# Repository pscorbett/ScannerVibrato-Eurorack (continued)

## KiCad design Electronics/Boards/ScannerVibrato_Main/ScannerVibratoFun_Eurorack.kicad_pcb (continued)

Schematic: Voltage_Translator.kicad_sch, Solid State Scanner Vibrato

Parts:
C45, C46: 100nF; C_0603_1608Metric
R3, R5, R6, R7, R8, R9: 100k; R_0603_1608Metric
U33: LM339; TSSOP-14_4.4x5mm_P0.65mm; Part Number LM339APWR

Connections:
+5V: R3.1; also elsewhere on the board
+9V: C45.1, R6.1, R7.1, R8.1, R9.1, U33.3 (V+); also elsewhere on the board
-9V: C46.2, U33.12 (V-); also elsewhere on the board
/Counters/TAP_MUXL_ODD_S0: U33.5 (+); also elsewhere on the board
/Counters/TAP_MUXL_ODD_S1: U33.7 (+); also elsewhere on the board
/Counters/TAP_MUXL_ODD_S2: U33.11 (+); also elsewhere on the board
/Counters/TAP_MUXL_ODD_S3: U33.9 (+); also elsewhere on the board
/Counters/X_TAP_MUXL_ODD_S0: R6.2, U33.2; also elsewhere on the board
/Counters/X_TAP_MUXL_ODD_S1: R7.2, U33.1; also elsewhere on the board
/Counters/X_TAP_MUXL_ODD_S2: R8.2, U33.13; also elsewhere on the board
/Counters/X_TAP_MUXL_ODD_S3: R9.2, U33.14; also elsewhere on the board
GND: C45.2, C46.1, R5.2; also elsewhere on the board
unnamed: R3.2, R5.1, U33.4 (-), U33.6 (-), U33.8 (-), U33.10 (-)

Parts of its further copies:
C49, C50, C53, C54, C57, C58: 100nF; C_0603_1608Metric
R10, R11, R12, R13, R14, R15, R16, R17, R18, R19, R20, R21, R22, R23, R24, R25, R26, R31: 100k; R_0603_1608Metric
U34, U35, U36: LM339; TSSOP-14_4.4x5mm_P0.65mm; Part Number LM339APWR

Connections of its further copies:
+5V: R10.1, R16.1, R22.1; also elsewhere on the board
+9V: C49.1, C53.1, C57.1, R12.1, R13.1, R14.1, R15.1, R18.1, R19.1, R20.1, R21.1, R24.1, R25.1, R26.1, R31.1, U34.3 (V+), U35.3 (V+), U36.3 (V+); also elsewhere on the board
-9V: C50.2, C54.2, C58.2, U34.12 (V-), U35.12 (V-), U36.12 (V-); also elsewhere on the board
/Counters/TAP_MUXL_EVEN_S0: U34.5 (+); also elsewhere on the board
/Counters/TAP_MUXL_EVEN_S1: U34.7 (+); also elsewhere on the board
/Counters/TAP_MUXL_EVEN_S2: U34.11 (+); also elsewhere on the board
/Counters/TAP_MUXL_EVEN_S3: U34.9 (+); also elsewhere on the board
/Counters/TAP_MUXR_EVEN_S0: U36.5 (+); also elsewhere on the board
/Counters/TAP_MUXR_EVEN_S1: U36.7 (+); also elsewhere on the board
/Counters/TAP_MUXR_EVEN_S2: U36.11 (+); also elsewhere on the board
/Counters/TAP_MUXR_EVEN_S3: U36.9 (+); also elsewhere on the board
/Counters/TAP_MUXR_ODD_S0: U35.5 (+); also elsewhere on the board
/Counters/TAP_MUXR_ODD_S1: U35.7 (+); also elsewhere on the board
/Counters/TAP_MUXR_ODD_S2: U35.11 (+); also elsewhere on the board
/Counters/TAP_MUXR_ODD_S3: U35.9 (+); also elsewhere on the board
/Counters/X_TAP_MUXL_EVEN_S0: R12.2, U34.2; also elsewhere on the board
/Counters/X_TAP_MUXL_EVEN_S1: R13.2, U34.1; also elsewhere on the board
/Counters/X_TAP_MUXL_EVEN_S2: R14.2, U34.13; also elsewhere on the board
/Counters/X_TAP_MUXL_EVEN_S3: R15.2, U34.14; also elsewhere on the board
/Counters/X_TAP_MUXR_EVEN_S0: R24.2, U36.2; also elsewhere on the board
/Counters/X_TAP_MUXR_EVEN_S1: R25.2, U36.1; also elsewhere on the board
/Counters/X_TAP_MUXR_EVEN_S2: R26.2, U36.13; also elsewhere on the board
/Counters/X_TAP_MUXR_EVEN_S3: R31.2, U36.14; also elsewhere on the board
/Counters/X_TAP_MUXR_ODD_S0: R18.2, U35.2; also elsewhere on the board
/Counters/X_TAP_MUXR_ODD_S1: R19.2, U35.1; also elsewhere on the board
/Counters/X_TAP_MUXR_ODD_S2: R20.2, U35.13; also elsewhere on the board
/Counters/X_TAP_MUXR_ODD_S3: R21.2, U35.14; also elsewhere on the board
GND: C49.2, C50.1, C53.2, C54.1, C57.2, C58.1, R11.2, R17.2, R23.2; also elsewhere on the board
unnamed: R10.2, R11.1, U34.4 (-), U34.6 (-), U34.8 (-), U34.10 (-)
unnamed: R16.2, R17.1, U35.4 (-), U35.6 (-), U35.8 (-), U35.10 (-)
unnamed: R22.2, R23.1, U36.4 (-), U36.6 (-), U36.8 (-), U36.10 (-)

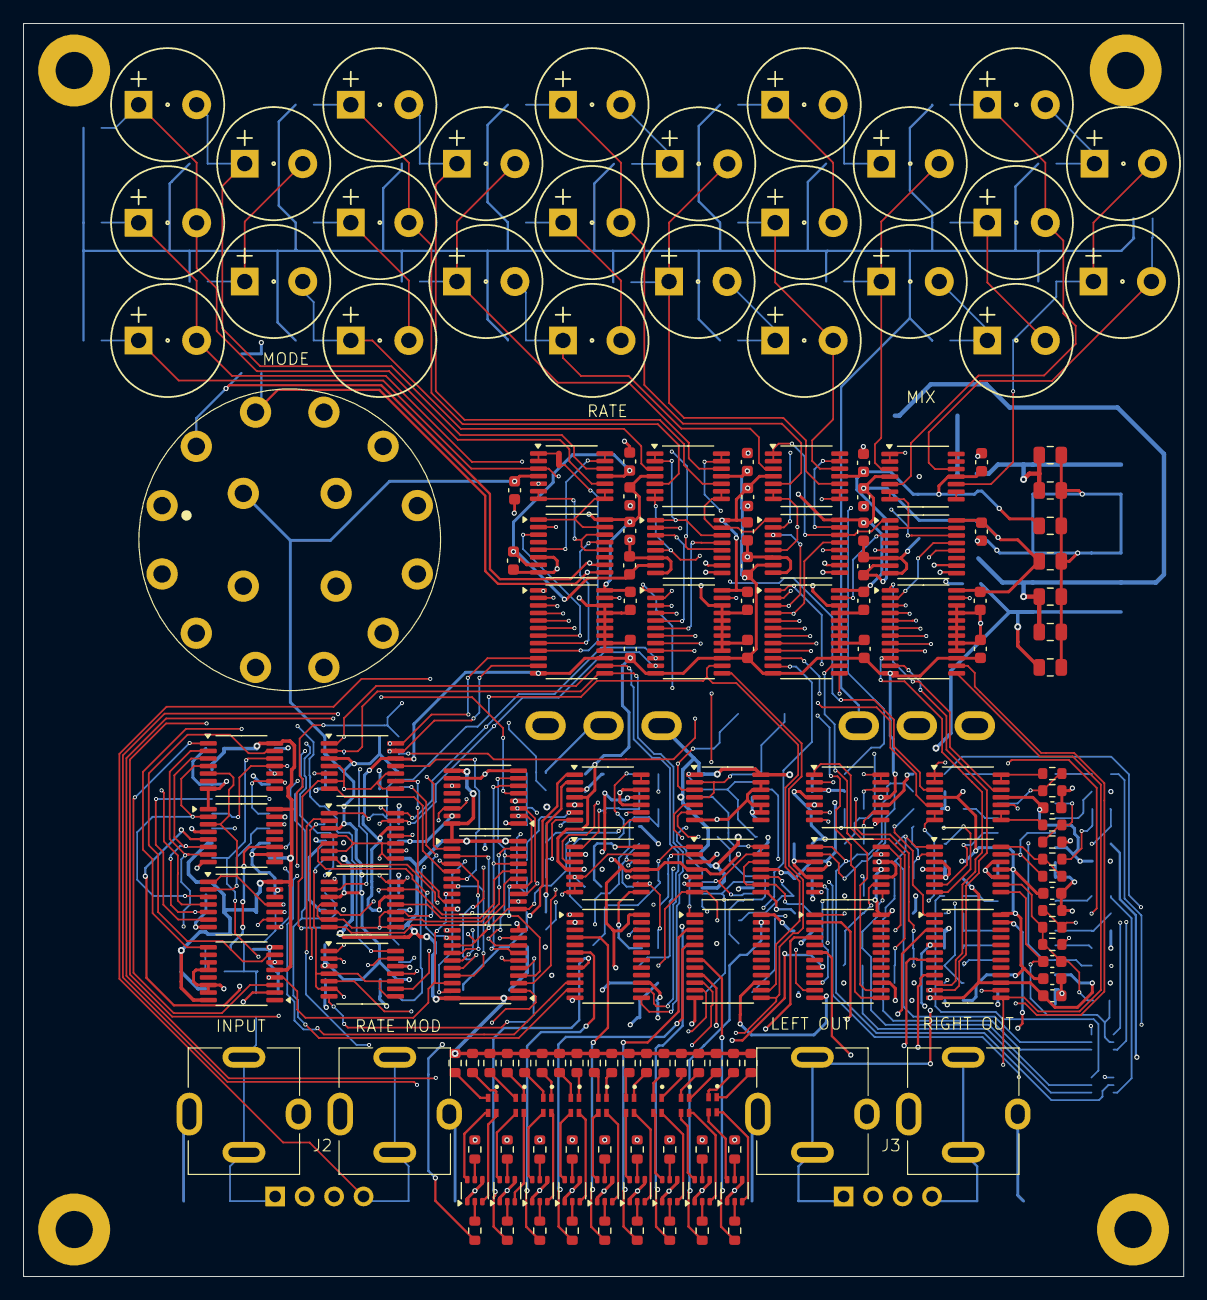
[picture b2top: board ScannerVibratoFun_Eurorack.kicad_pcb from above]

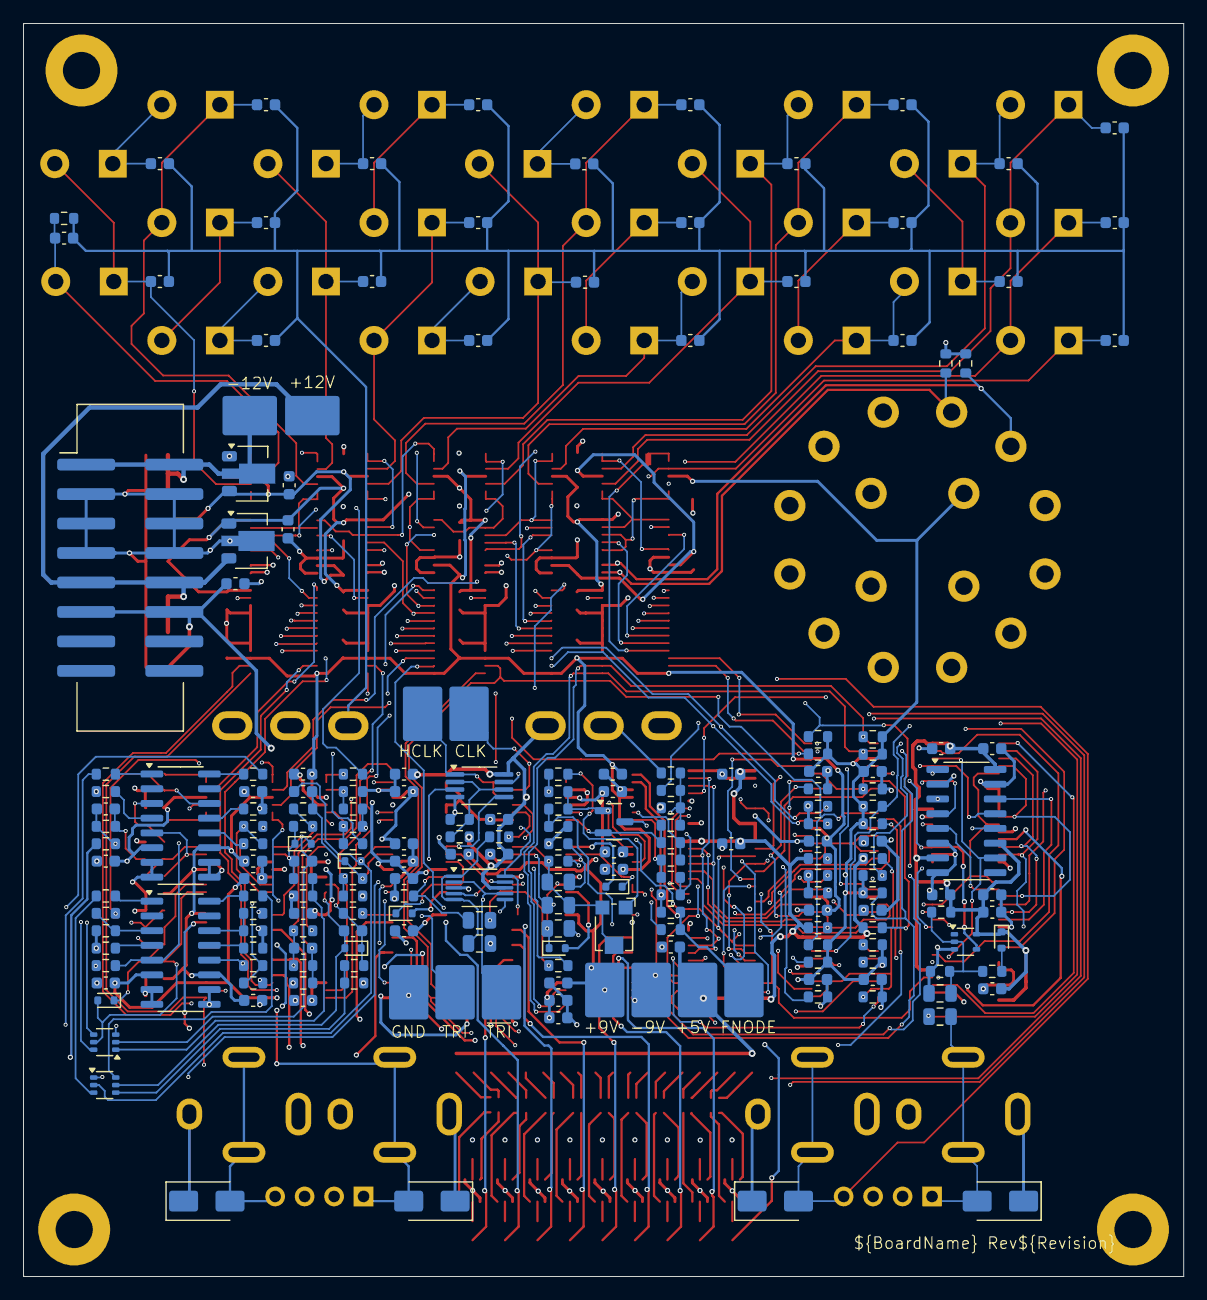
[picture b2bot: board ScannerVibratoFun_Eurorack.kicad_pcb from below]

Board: 4 copper layers, 100.0 x 108.0 mm, 371 parts (206 on the bottom side), 280 nets.

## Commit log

2025-02-09 Create LICENCE.md
    Dual licence to cover hardware under CERN 2.0 and code under GPL3
2025-08-02 Adding main and IO PCBs
2025-08-02 Adding Digital (logic) and Falstad (circuit) simulations
2025-08-02 Adding mechanical (FreeCAD) files and tap table
